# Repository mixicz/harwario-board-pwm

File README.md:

# Universal PWM board for Hardwario TOWER
There are many PWM controlled applications, from driving LED strips or fans to controlling servos. Purpose of this board is to allow for wide range of use cases, so you can get bunch of them professionally manufactured (which is usually much cheaper when you order more of them) and customize it to particular use just by fitting right components.

I had several requirements:
- low profile (I sometimes need to fit it in slim places),
- wide range of input voltage, at least 5-24V,
- able to handle decent current for driving LED strips,
- any output can be configured to GND, VCC or PWM,
- any core module GPIO output can be connected to any output (not all outputs support PWM),
- optional mini battery module including battery level monitoring (so you can keep communicating even after power outage),
- possibility to route battery level signals to non-PWM ADC inputs (P4, P5),
- proper handling of Hardwario TOWER power signals (so you can use USB to update firmware or debug without need of disconnecting PSU),
- optional use of Adafruit I2C PWM module instead of direct GPIO (https://www.adafruit.com/product/815).

For discussion regarding board design see Hardwario Forum topic https://forum.hardwario.com/t/universal-pcb-1-pwm/655

## Features
- 5-35V input,
- should be able to handle up to ~8A total or ~4A per output pair using 70µm copper (or ~5A total + ~3A per output for 35µm copper),
- all SMD components were selected large enough to be easily soldered by hand,

Physical dimensions 100×80 mm, holes 3.2 mm wide, placed 4 mm from each side.

## HW configuration
For power input and output use connectors or headers with 5mm spacing (and proper power rating according to your needs). In case your connectors does not fit side to side and you cannot leave unused output between, you can place them on both sides of board.

### Required components
These components needs to be fitted in all cases:
- input power terminal (on short side of the board),
- core module header (CORE) - you need to use socket header here to fit core module pin side,
- PSU section: AP1501 step down + **L1**, **D1**, **D4**, **C1**, **C2**
- Tower power control signals: **D3**, **R3** 

### Configuring general board features
1. If you want to use battery module, you need to fit pin headers to **BATT** and **D2**+**R2** for *BAT_OFF* signal. You may also use 0R SMD resistors **R4**+**R5** to allow for battery level measure (this is default assigment, you will loose 2 usable PWM pins though) or alternativelly use **R6**+**R7** to connect it to *P4*+*P5* pins (which does not have PWM capability).
2. If you want to monitor input power status (for example to send message on power outage and restore), you can use **R1** for this.

### Configuring outputs
Each output has place for four resistors (Rx1 - Rx4, where *x* is output number) and one SO-8 N-channel MOSFET transistor (IRF7413).

1. First assign function to each output according to your needs (I recommend to not use even-numbered transistors for high curent outputs in order to leave room for better vias cooling),
2. Decide which PWM outputs from core module to use (not all GPIO does support PWM - see https://tower.hardwario.com/en/latest/hardware/header-pinout/). GPIO are mapped to board P0-P15 starting from side with power input connector.
3. Connect desired core module PWM GPIO to particular outputs using **Rx1** (small resistor 0-390 ohm or just wire). You can generally connect any GPIO to any output, just be carefull to not short-circuit signals when you have uninsulated wires close together.
4. for each used output fit one of:
    - PWM: **Rx2** + transistor **Tx**
    - VCC: **Rx4**
    - GND: **Rx3**
    
### Using Adafruit I2C 16-Channel 12-bit PWM module
Alternatively, instead of directly routing core module GPIO, you can use [Adafruit I2C 16-Channel 12-bit PWM](https://www.adafruit.com/product/815) module. In such case, place 4× 4-pin socket header in **Rx1** holes closer to the outputs (it will fit to PWM outputs from the module) and 6-pin socket header to **JP3** position. Outputs are configured in same manner as mentioned above.

# Part list
## Required
| **component** | **part / value** | 
| ----------- | ----------- |
| step-down | AP1501 (TO263-5L) | 
| C1 | 10µF 16V |
| C2 | 10µF 35V |
| L1 | 33µH (THT) |
| D1 | B340A (SMA) |
| D3, D4 | PMLL41* or similar (SOD80C) diode |
| R3 | 560R (R3216 EU) |
| Rx2 | N× 10k (R3216 EU) |
| Tx | N× IRF7413 (SO8) |
| JP1 (input) | 2-wire 5.08 mm spaced connector / terminal |
| JP2* (outputs) | N× 5.08 mm spaced connector / terminal as needed |
| header - core module | 14-pin, 8-pin and 5-pin 1-row socket header (2.54 mm spaced) |
| core module | [Hardwario TOWER core module](https://shop.hardwario.com/core-module/)

## Optional
| **component** | **part / value** | 
| ----------- | ----------- |
| Rx1 | wire or 0-390R THT resistor |
| R4-7, Rx3, Rx4 | 0R (R3216 EU) |
| R1, R2 | 560R (R3216 EU) |
| D2 | PMLL41* or similar (SOD80C) diode |
| header - battery module | 14-pin, 8-pin and 5-pin 1-row socket header (2.54 mm spaced) |
| mini battery module | [Hardwario TOWER mini battery module](https://shop.hardwario.com/mini-battery-module/)
| header - PWM module | 1× 6-pin + 4× 4-pin socket header (2.54 mm spaced) |
| PWM module | [Adafruit I2C 16-Channel 12-bit PWM](https://www.adafruit.com/product/815)

# Known issues
## v 1.0
- Battery module needs higher header (at least 6mm) because of:
    - C1 is too close to battery module header (it can be placed on the other side as workaround),
    - R142, R162 are right below battery connector on module, risking short circuit,
- L1 has too small footprint for most inductors available,
- signal paths are only 0.3mm wide which complicates manufacturing with thicker Cu plating (70 µm or more).

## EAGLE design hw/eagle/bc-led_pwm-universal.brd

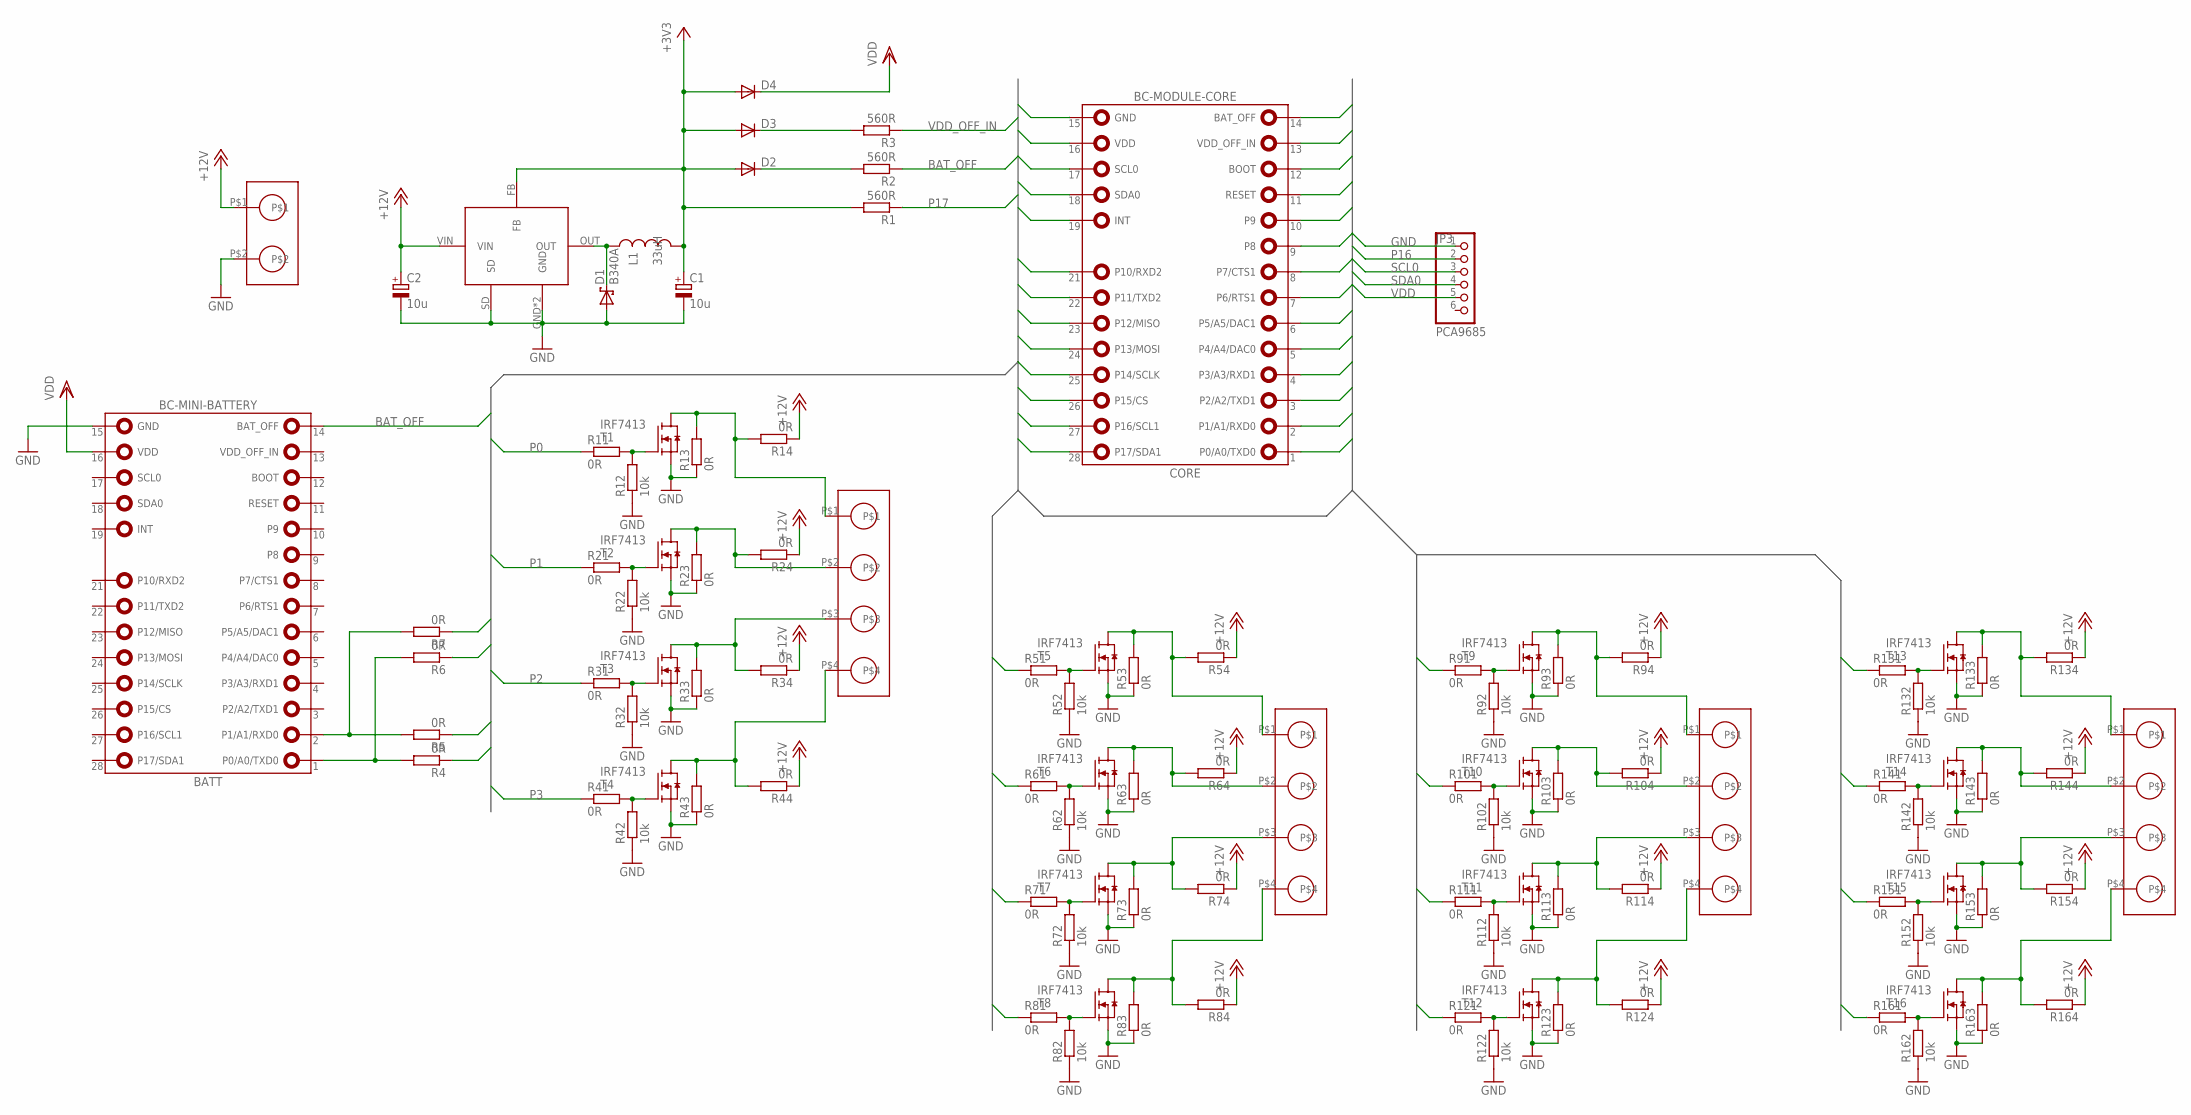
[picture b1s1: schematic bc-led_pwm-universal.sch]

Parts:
BATT: BC-MINI-BATTERY; BC-MODULE-CORE
C1: 10u; E1,8-4
C2: 10u; E2-5
CORE: BC-MODULE-CORE
D1: B340A; SMB
D2, D3, D4: PMLL41SOD80C; SOD80C
JP1: STLZ950/2G-5.08-H; HDR-5.08-1_2
JP2A, JP2B, JP2C, JP2D: STLZ950/4G-5.08-V; HDR-5.08-1_4
JP3: PCA9685; 1X06
L1: 33uH; BC12
R1, R2, R3: 560R; R3216
R4, R5, R6, R7, R13, R14, R23, R24, R33, R34, R43, R44, R53, R54, R63, R64, R73, R74, R83, R84, R93, R94, R103, R104, R113, R114, R123, R124, R133, R134, R143, R144, R153, R154, R163, R164: 0R; R3216
R11, R21, R31, R41, R51, R61, R71, R81, R91, R101, R111, R121, R131, R141, R151, R161: 0R; 0207/7
R12, R22, R32, R42, R52, R62, R72, R82, R92, R102, R112, R122, R132, R142, R152, R162: 10k; R3216
T1, T2, T3, T4, T5, T6, T7, T8, T9, T10, T11, T12, T13, T14, T15, T16: IRF7413; SO8
U$1: AP1501; TO263-5L

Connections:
+3V3: C1.+, D2.A, D3.A, D4.A, L1.2, R1.2, U$1.FB
+12V: C2.+, JP1.P$1, R14.1, R24.1, R34.1, R44.1, R54.1, R64.1, R74.1, R84.1, R94.1, R104.1, R114.1, R124.1, R134.1, R144.1, R154.1, R164.1, U$1.VIN
BAT_OFF: BATT.14 (BAT_OFF), CORE.14 (BAT_OFF), R2.1
BOOT: CORE.12 (BOOT)
GND: BATT.15 (GND), C1.-, C2.-, CORE.15 (GND), D1.A, JP1.P$2, JP3.1, R12.1, R13.1, R22.1, R23.1, R32.1, R33.1, R42.1, R43.1, R52.1, R53.1, R62.1, R63.1, R72.1, R73.1, R82.1, R83.1, R92.1, R93.1, R102.1, R103.1, R112.1, R113.1, R122.1, R123.1, R132.1, R133.1, R142.1, R143.1, R152.1, R153.1, R162.1, R163.1, T1.1 (S), T1.2 (S), T1.3 (S), T2.1 (S), T2.2 (S), T2.3 (S), T3.1 (S), T3.2 (S), T3.3 (S), T4.1 (S), T4.2 (S), T4.3 (S), T5.1 (S), T5.2 (S), T5.3 (S), T6.1 (S), T6.2 (S), T6.3 (S), T7.1 (S), T7.2 (S), T7.3 (S), T8.1 (S), T8.2 (S), T8.3 (S), T9.1 (S), T9.2 (S), T9.3 (S), T10.1 (S), T10.2 (S), T10.3 (S), T11.1 (S), T11.2 (S), T11.3 (S), T12.1 (S), T12.2 (S), T12.3 (S), T13.1 (S), T13.2 (S), T13.3 (S), T14.1 (S), T14.2 (S), T14.3 (S), T15.1 (S), T15.2 (S), T15.3 (S), T16.1 (S), T16.2 (S), T16.3 (S), U$1.GND, U$1.GND2 (GND), U$1.SD
INT: CORE.19 (INT)
unnamed: R11.2, R12.2, T1.4 (G)
unnamed: JP2A.P$1, R13.2, R14.2, T1.5 (D), T1.6 (D), T1.7 (D), T1.8 (D)
unnamed: BATT.2 (P1/A1/RXD0), R5.2, R7.2
unnamed: BATT.1 (P0/A0/TXD0), R4.2, R6.2
unnamed: D1.C, L1.1, U$1.OUT
unnamed: R31.2, R32.2, T3.4 (G)
unnamed: JP2A.P$3, R33.2, R34.2, T3.5 (D), T3.6 (D), T3.7 (D), T3.8 (D)
unnamed: R21.2, R22.2, T2.4 (G)
unnamed: JP2A.P$2, R23.2, R24.2, T2.5 (D), T2.6 (D), T2.7 (D), T2.8 (D)
unnamed: R41.2, R42.2, T4.4 (G)
unnamed: JP2A.P$4, R43.2, R44.2, T4.5 (D), T4.6 (D), T4.7 (D), T4.8 (D)
unnamed: D2.C, R2.2
unnamed: D3.C, R3.2
unnamed: R51.2, R52.2, T5.4 (G)
unnamed: JP2B.P$1, R53.2, R54.2, T5.5 (D), T5.6 (D), T5.7 (D), T5.8 (D)
unnamed: R61.2, R62.2, T6.4 (G)
unnamed: JP2B.P$2, R63.2, R64.2, T6.5 (D), T6.6 (D), T6.7 (D), T6.8 (D)
unnamed: R71.2, R72.2, T7.4 (G)
unnamed: JP2B.P$3, R73.2, R74.2, T7.5 (D), T7.6 (D), T7.7 (D), T7.8 (D)
unnamed: R81.2, R82.2, T8.4 (G)
unnamed: JP2B.P$4, R83.2, R84.2, T8.5 (D), T8.6 (D), T8.7 (D), T8.8 (D)
unnamed: R91.2, R92.2, T9.4 (G)
unnamed: JP2C.P$1, R93.2, R94.2, T9.5 (D), T9.6 (D), T9.7 (D), T9.8 (D)
unnamed: R101.2, R102.2, T10.4 (G)
unnamed: JP2C.P$2, R103.2, R104.2, T10.5 (D), T10.6 (D), T10.7 (D), T10.8 (D)
unnamed: R111.2, R112.2, T11.4 (G)
unnamed: JP2C.P$3, R113.2, R114.2, T11.5 (D), T11.6 (D), T11.7 (D), T11.8 (D)
unnamed: R121.2, R122.2, T12.4 (G)
unnamed: JP2C.P$4, R123.2, R124.2, T12.5 (D), T12.6 (D), T12.7 (D), T12.8 (D)
unnamed: R131.2, R132.2, T13.4 (G)
unnamed: JP2D.P$1, R133.2, R134.2, T13.5 (D), T13.6 (D), T13.7 (D), T13.8 (D)
unnamed: R141.2, R142.2, T14.4 (G)
unnamed: JP2D.P$2, R143.2, R144.2, T14.5 (D), T14.6 (D), T14.7 (D), T14.8 (D)
unnamed: R151.2, R152.2, T15.4 (G)
unnamed: JP2D.P$3, R153.2, R154.2, T15.5 (D), T15.6 (D), T15.7 (D), T15.8 (D)
unnamed: R161.2, R162.2, T16.4 (G)
unnamed: JP2D.P$4, R163.2, R164.2, T16.5 (D), T16.6 (D), T16.7 (D), T16.8 (D)
P0: CORE.1 (P0/A0/TXD0), R4.1, R11.1
P1: CORE.2 (P1/A1/RXD0), R5.1, R21.1
P2: CORE.3 (P2/A2/TXD1), R31.1
P3: CORE.4 (P3/A3/RXD1), R41.1
P4: CORE.5 (P4/A4/DAC0), R6.1, R51.1
P5: CORE.6 (P5/A5/DAC1), R7.1, R61.1
P6: CORE.7 (P6/RTS1), R71.1
P7: CORE.8 (P7/CTS1), R81.1
P8: CORE.9 (P8), R91.1
P9: CORE.10 (P9), R101.1
P10: CORE.21 (P10/RXD2), R111.1
P11: CORE.22 (P11/TXD2), R121.1
P12: CORE.23 (P12/MISO), R131.1
P13: CORE.24 (P13/MOSI), R141.1
P14: CORE.25 (P14/SCLK), R151.1
P15: CORE.26 (P15/CS), R161.1
P16: CORE.27 (P16/SCL1), JP3.2
P17: CORE.28 (P17/SDA1), R1.1
RESET: CORE.11 (RESET)
SCL0: CORE.17 (SCL0), JP3.3
SDA0: CORE.18 (SDA0), JP3.4
VDD: BATT.16 (VDD), CORE.16 (VDD), D4.C, JP3.5
VDD_OFF_IN: CORE.13 (VDD_OFF_IN), R3.1

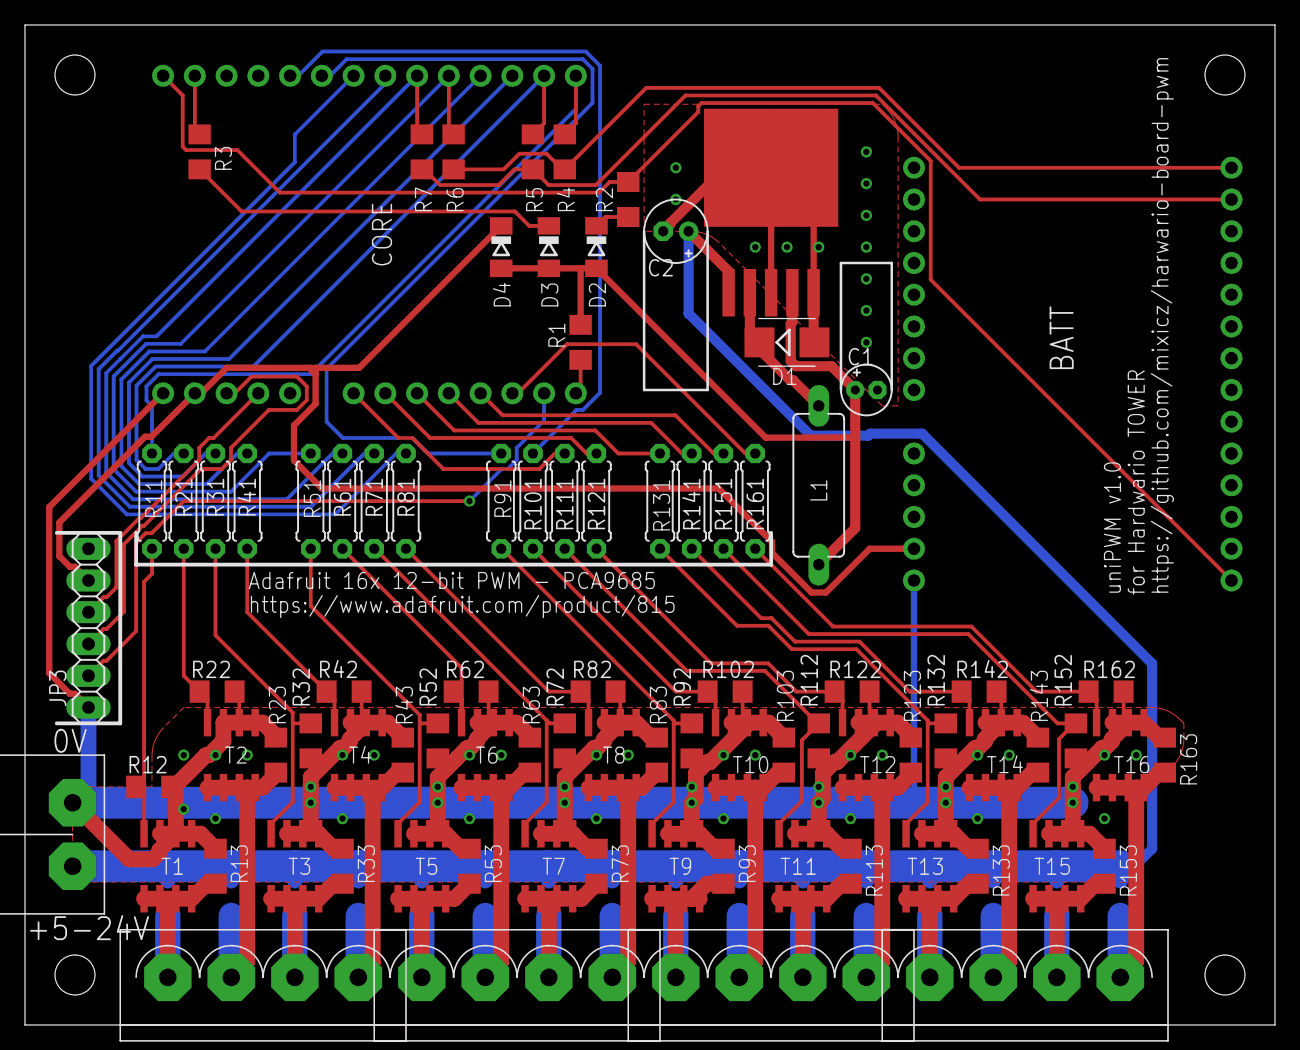
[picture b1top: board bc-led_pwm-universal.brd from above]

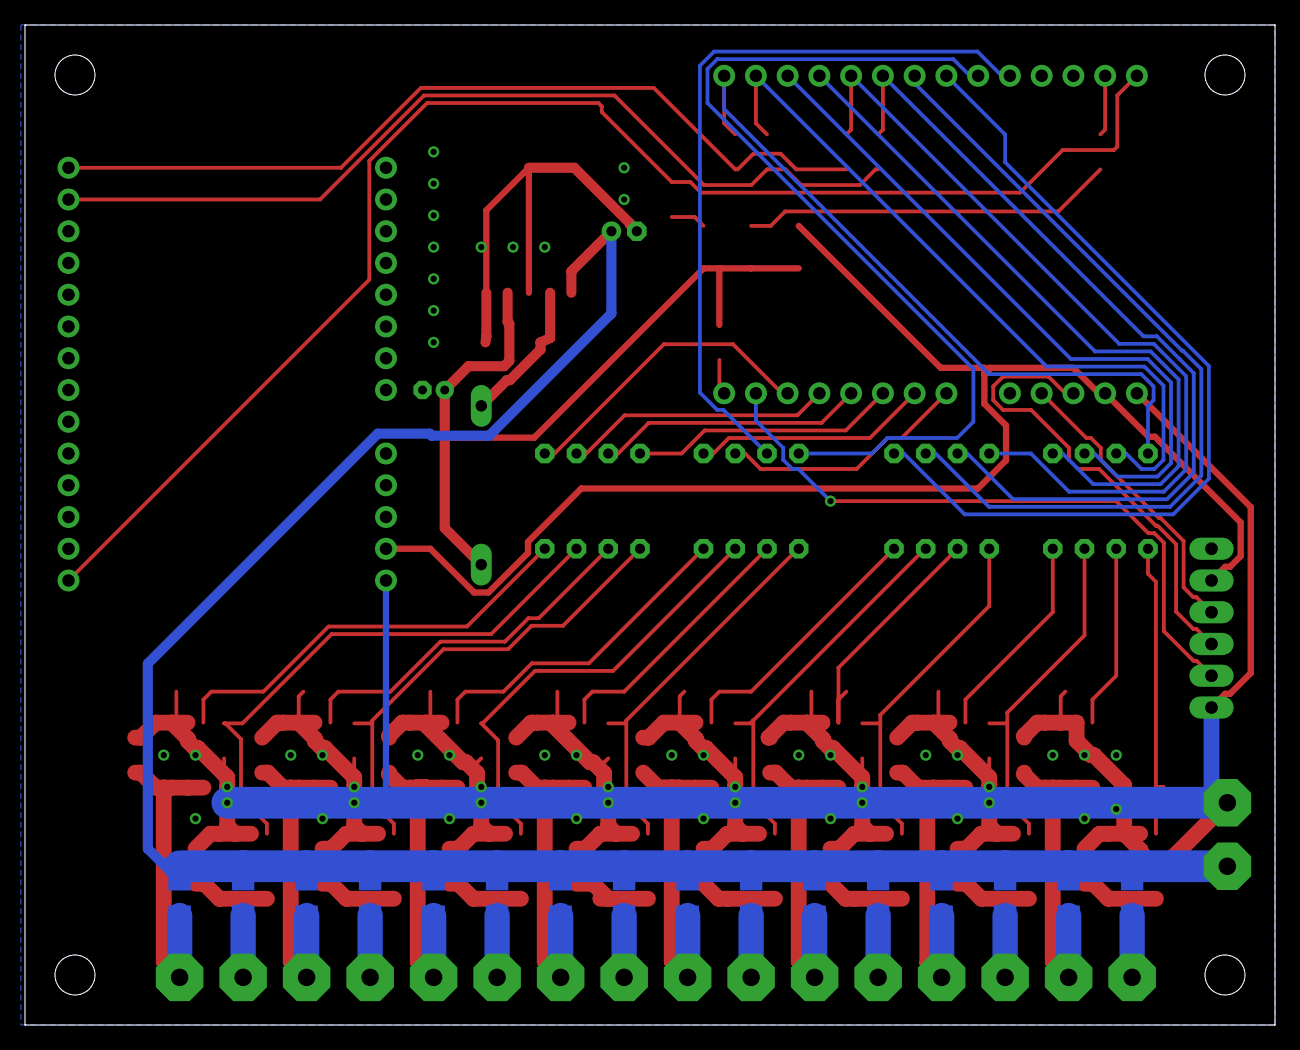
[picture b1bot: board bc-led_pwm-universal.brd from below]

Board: 2 copper layers, 100.0 x 80.0 mm, 103 parts (17 on the bottom side), 63 nets.

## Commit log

2021-07-12 rotate core module to have convenient access to USB port, added pull-down resistors on output FETs, proper VDD_OFF handling and added power outage monitoring via P17
2021-07-14 added ground plane, reworked step-down
2021-07-14 fixes from DRC
2021-07-15 Changed 0R on FET gates, fixed symbols for schottky & inductor
2021-07-20 ignore CAM output directory
2021-07-20 added documentation
2021-07-20 onboard descriptions
2021-07-21 added names and partlist
2021-08-04 list known issues
2022-06-01 some updates (cant remember which)
2024-01-12 added kicad import cache to ignore list
